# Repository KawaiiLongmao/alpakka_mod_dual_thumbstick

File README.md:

Development Board : rp2040 zero

初版：

GP20(Home)->GP13,GP18(CS0)->GP0,GP19(CS1)->GP1

led：上移12.5mm

r6电阻：左移21.5mm，上移4.75mm

home：上移22.5mm

滚轮：左移16mm

两摇杆间距：51.75mm

修订1：

GP20(Home)->GP13,GP18(CS0)->GP0,GP19(CS1)->GP1

led：上移12.5mm

r6电阻：左移21.5mm，上移4.75mm

home：上移22.5mm

滚轮：左移18.5mm

左摇杆：左移2.5mm

两摇杆间距：52mm

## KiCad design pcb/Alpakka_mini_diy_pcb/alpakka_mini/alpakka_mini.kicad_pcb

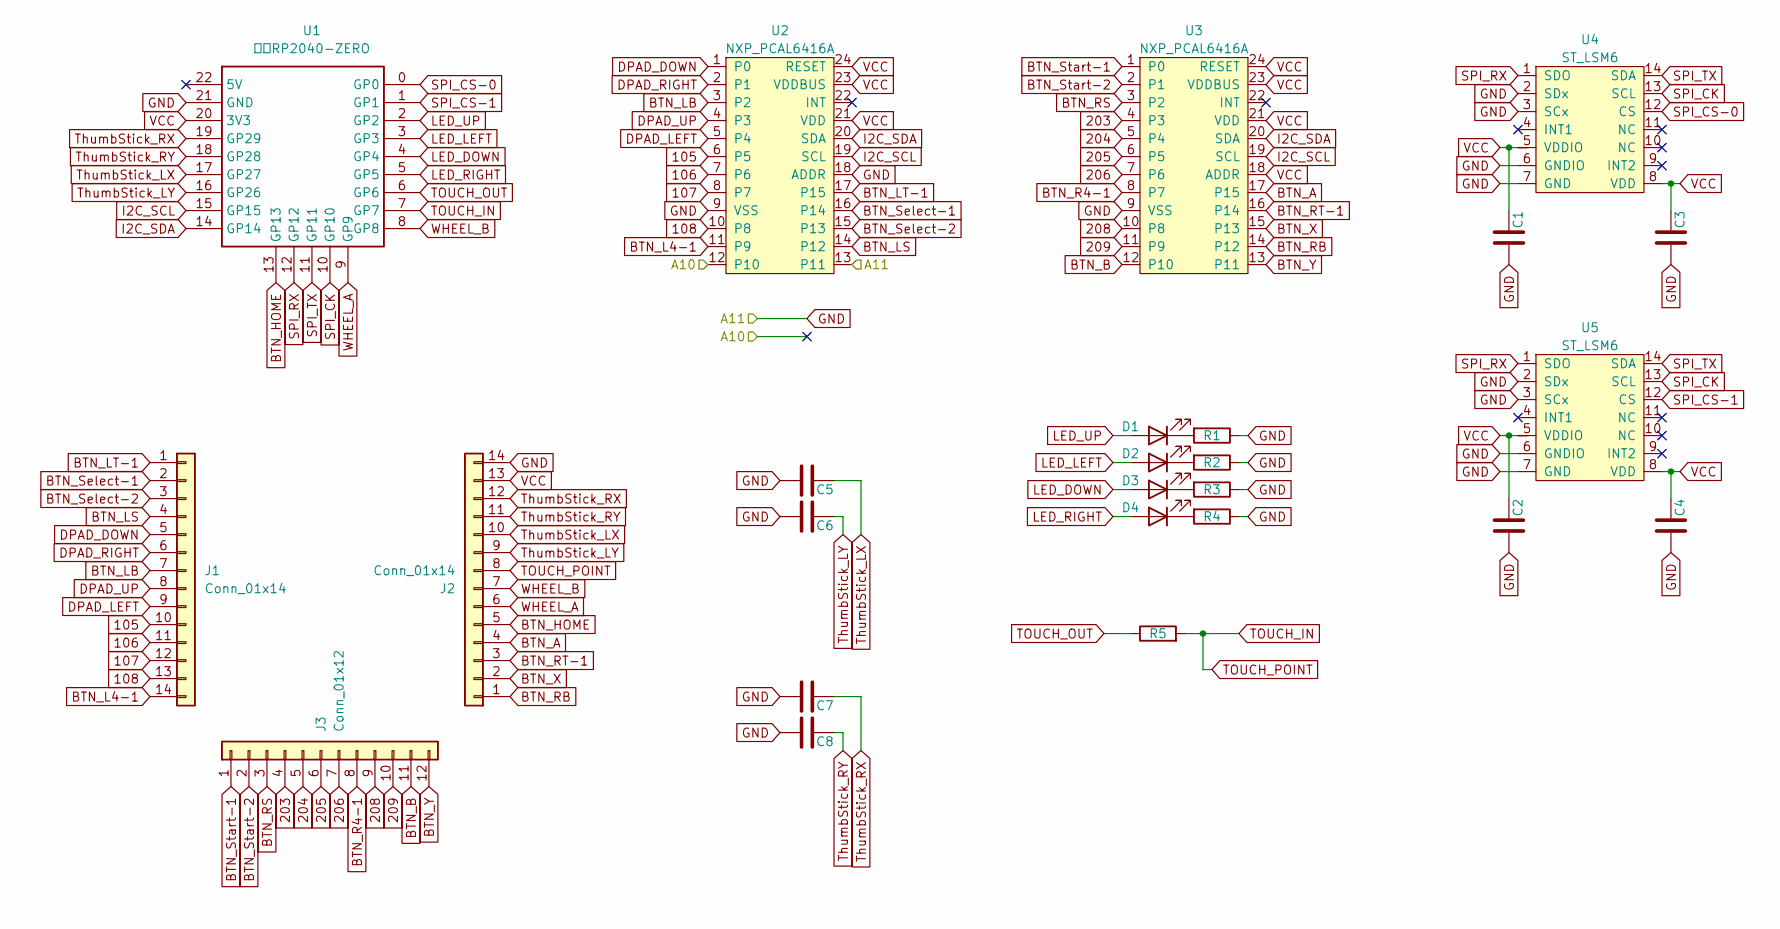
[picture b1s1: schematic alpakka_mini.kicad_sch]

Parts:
C1, C2, C3, C4, C5, C6, C7, C8: C; 0402; LCSC C1525
D1, D2, D3, D4: Diode; 0603_d; LCSC C2290
J1, J2: Conn_01x14; 邮票孔排针1x14PIN_2.54MM
J3: Conn_01x12; 邮票孔排针1x12PIN_2.54MM
R1, R2, R3, R4: R; 0603; LCSC C22950
R5: R6; 0402; LCSC C11616
U1: 微雪RP2040-ZERO; RP2040-ZERO_SMT
U2, U3: NXP_PCAL6416A; QFN24; LCSC C2652287
U4, U5: ST_LSM6; LGA14; LCSC C784817

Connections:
105: J1.10, U2.6 (P5)
106: J1.11, U2.7 (P6)
107: J1.12, U2.8 (P7)
108: J1.13, U2.10 (P8)
203: J3.4, U3.4 (P3)
204: J3.5, U3.5 (P4)
205: J3.6, U3.6 (P5)
206: J3.7, U3.7 (P6)
208: J3.9, U3.10 (P8)
209: J3.10, U3.11 (P9)
/A10: U2.12 (P10)
BTN_A: J2.4, U3.17 (P15)
BTN_B: J3.11, U3.12 (P10)
BTN_HOME: J2.5, U1.13 (GP13)
BTN_L4-1: J1.14, U2.11 (P9)
BTN_LB: J1.7, U2.3 (P2)
BTN_LS: J1.4, U2.14 (P12)
BTN_LT-1: J1.1, U2.17 (P15)
BTN_R4-1: J3.8, U3.8 (P7)
BTN_RB: J2.1, U3.14 (P12)
BTN_RS: J3.3, U3.3 (P2)
BTN_RT-1: J2.3, U3.16 (P14)
BTN_Select-1: J1.2, U2.16 (P14)
BTN_Select-2: J1.3, U2.15 (P13)
BTN_Start-1: J3.1, U3.1 (P0)
BTN_Start-2: J3.2, U3.2 (P1)
BTN_X: J2.2, U3.15 (P13)
BTN_Y: J3.12, U3.13 (P11)
DPAD_DOWN: J1.5, U2.1 (P0)
DPAD_LEFT: J1.9, U2.5 (P4)
DPAD_RIGHT: J1.6, U2.2 (P1)
DPAD_UP: J1.8, U2.4 (P3)
GND: C1.1, C2.1, C3.1, C4.1, C5.1, C6.1, C7.1, C8.1, J2.14, R1.1, R2.1, R3.1, R4.1, U1.21 (GND), U2.9 (VSS), U2.13 (P11), U2.18 (ADDR), U3.9 (VSS), U4.2 (SDx), U4.3 (SCx), U4.6 (GNDIO), U4.7 (GND), U5.2 (SDx), U5.3 (SCx), U5.6 (GNDIO), U5.7 (GND)
I2C_SCL: U1.15 (GP15), U2.19 (SCL), U3.19 (SCL)
I2C_SDA: U1.14 (GP14), U2.20 (SDA), U3.20 (SDA)
LED_DOWN: D3.2 (A), U1.4 (GP4)
LED_LEFT: D2.2 (A), U1.3 (GP3)
LED_RIGHT: D4.2 (A), U1.5 (GP5)
LED_UP: D1.2 (A), U1.2 (GP2)
unnamed: D1.1 (K), R1.2
unnamed: D2.1 (K), R2.2
unnamed: D3.1 (K), R3.2
unnamed: D4.1 (K), R4.2
SPI_CK: U1.10 (GP10), U4.13 (SCL), U5.13 (SCL)
SPI_CS-0: U1.0 (GP0), U4.12 (CS)
SPI_CS-1: U1.1 (GP1), U5.12 (CS)
SPI_RX: U1.12 (GP12), U4.1 (SDO), U5.1 (SDO)
SPI_TX: U1.11 (GP11), U4.14 (SDA), U5.14 (SDA)
TOUCH_IN: J2.8, R5.2, U1.7 (GP7)
TOUCH_OUT: R5.1, U1.6 (GP6)
ThumbStick_LX: C5.2, J2.10, U1.17 (GP27)
ThumbStick_LY: C6.2, J2.9, U1.16 (GP26)
ThumbStick_RX: C7.2, J2.12, U1.19 (GP29)
ThumbStick_RY: C8.2, J2.11, U1.18 (GP28)
VCC: C1.2, C2.2, C3.2, C4.2, J2.13, U1.20 (3V3), U2.21 (VDD), U2.23 (VDDBUS), U2.24 (RESET), U3.18 (ADDR), U3.21 (VDD), U3.23 (VDDBUS), U3.24 (RESET), U4.5 (VDDIO), U4.8 (VDD), U5.5 (VDDIO), U5.8 (VDD)
WHEEL_A: J2.6, U1.9 (GP9)
WHEEL_B: J2.7, U1.8 (GP8)

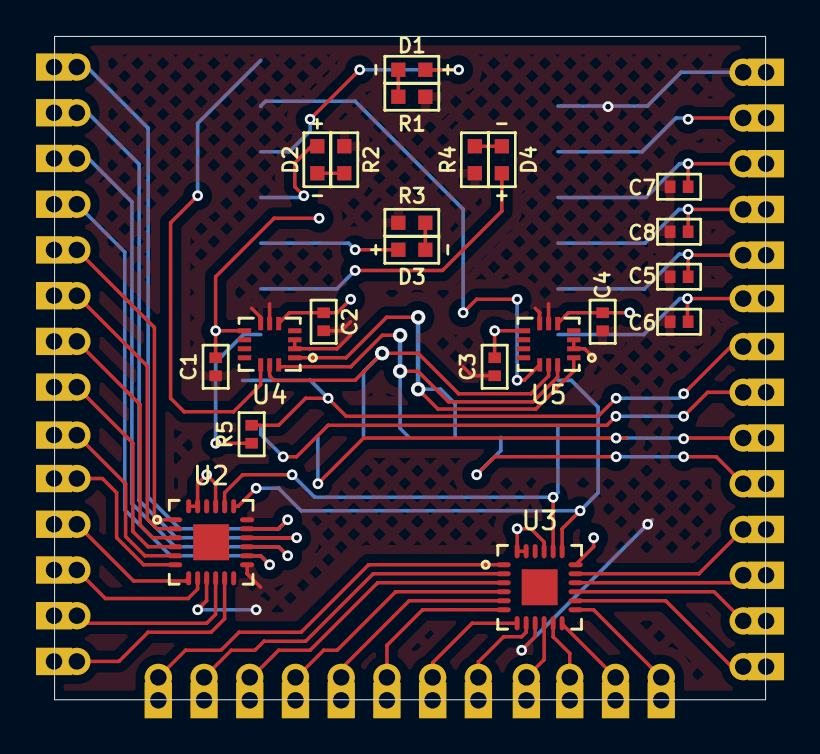
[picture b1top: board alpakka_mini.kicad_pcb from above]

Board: 2 copper layers, 39.5 x 36.9 mm, 25 parts (1 on the bottom side), 56 nets.

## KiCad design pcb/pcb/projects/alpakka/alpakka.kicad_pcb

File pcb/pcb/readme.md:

# Alpakka PCB

*Alpakka controller Printed Circuit Board reference design*

## Project links
- [Alpakka Manual](https://inputlabs.io/devices/alpakka/manual).
- [Alpakka Firmware](https://github.com/inputlabs/alpakka_firmware).
- [Alpakka PCB](https://github.com/inputlabs/alpakka_pcb). _(you are here)_
- [Alpakka 3D-print](https://github.com/inputlabs/alpakka_case).
- [Input Labs Roadmap](https://github.com/orgs/inputlabs/projects/2/views/2).

## Previews

## Order a PCB from the reference design
For ordering a reference design PCB (with no modifications) is possible to use the pre-built [order files](https://github.com/inputlabs/alpakka_pcb/releases). Check the [manual](https://inputlabs.io/devices/alpakka/manual/diy_pcb) for step-by-step instructions.

## Modify the schematics and PCB

### Dependencies
- [KiCad 8](https://www.kicad.org)

### Change components for SMT pick & place

- Open `.kicad_sch` file in Schematics editor.
- Go to menu `Tools` → `Edit symbol fields`
- Group by field `Group`
- Change id references (`LCSC id` for [JLCPCB](https://jlcpcb.com)).

### Generate order files from sources
- Copy `plugins/kicad_ilo_export.py` into KiCad plugins folder (PCB editor → menu `Tools` → `External plugins` → `Reveal plugins folder`).
- Open `.kicad_pcb` file in PCB editor.
- Use menu `Edit` → `Fill all zones`
- Go to menu `Tools` → `External plugins` → `Refresh plugins`
- Go to menu `Tools` → `External plugins` → `Input Labs: export`
- Files are generated into `order/`

### If the plugin does not load correctly
- Open `Preferences` → `Action plugins`
- Check that the plugin is installed correctly / check errors.

### Procedural zones
Consolidated zones increase `.kicad_pcb` file size significantly, so instead is recommended to load and save the project without consolidation:

- After loading the PCB project: `Edit` → `Fill all zones`.
- Before saving the PCB project: `Edit` → `Unfill all zones`.

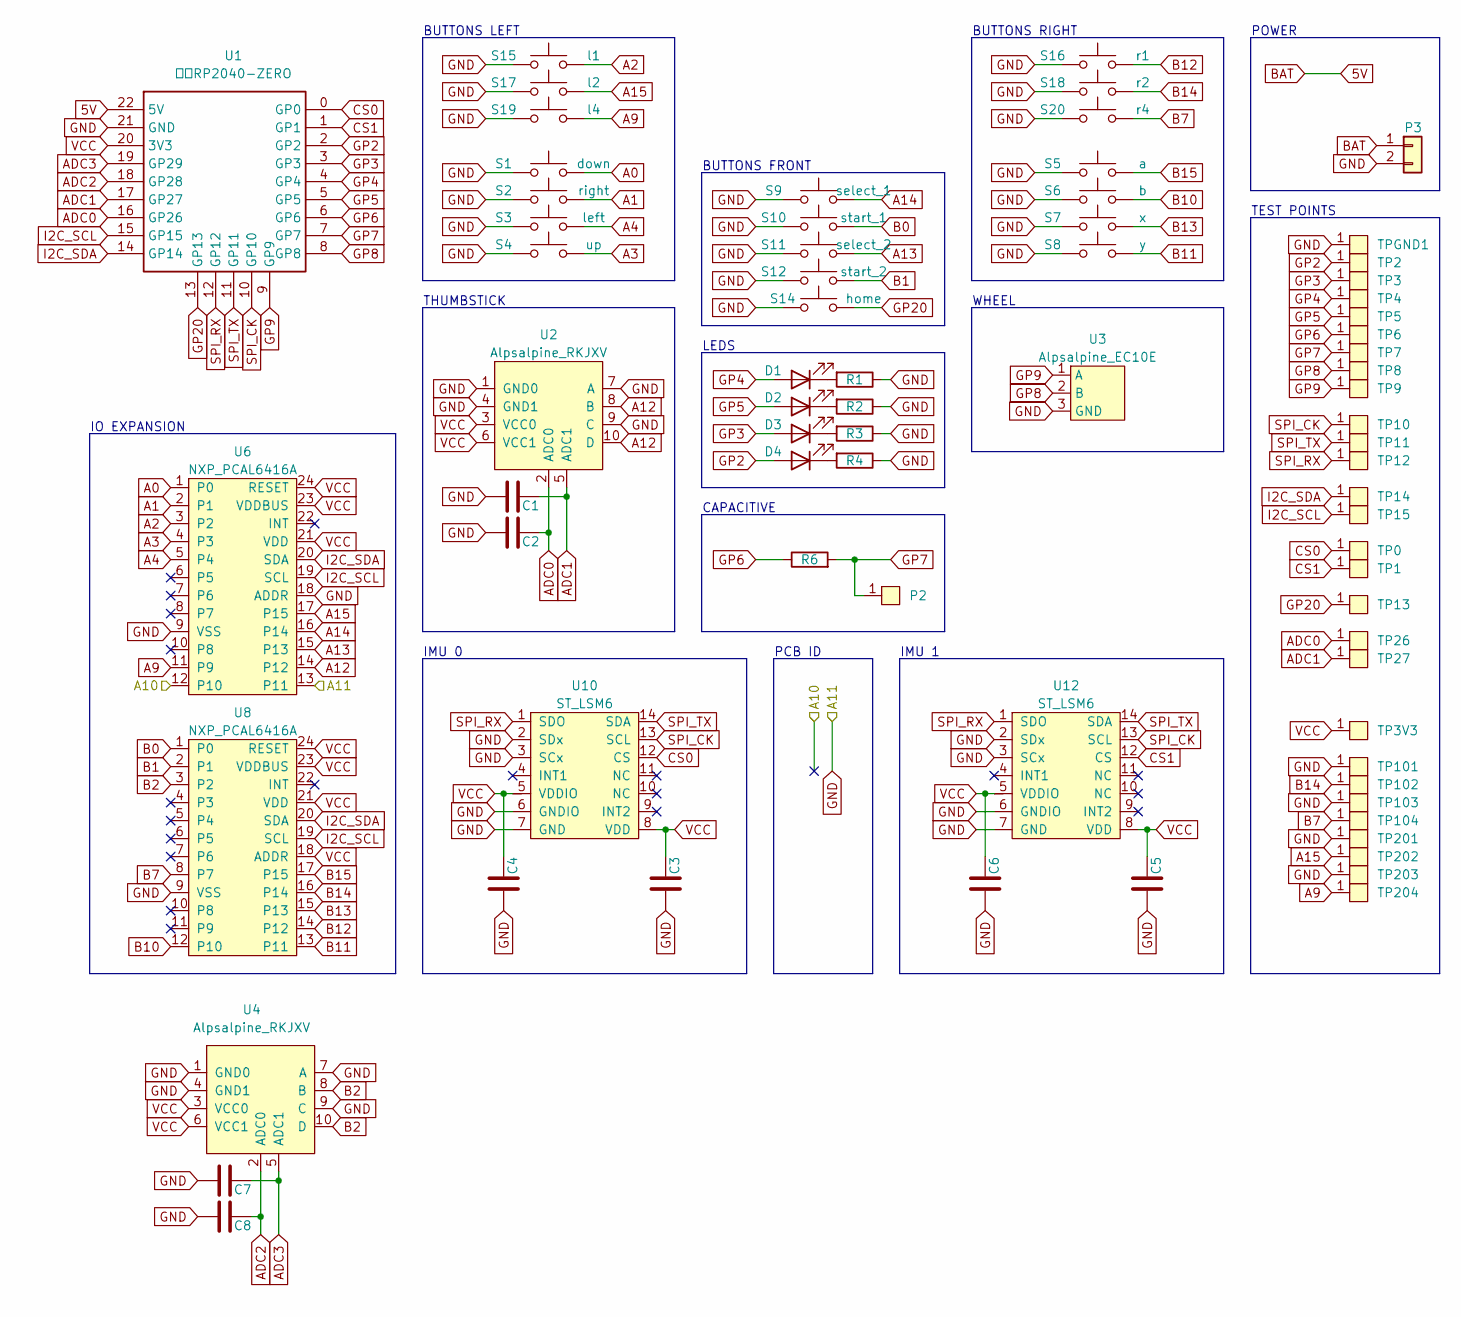
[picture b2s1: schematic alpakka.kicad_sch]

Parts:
C1, C2, C3, C4, C5, C6, C7, C8: C; 0402; LCSC C1525
D1, D2, D3, D4: Diode; 0603_d; LCSC C2290
P2: Endpoint; HRO_BC-25-3P; LCSC C707322
P3: Conn_01x02; JST_PH_2_TH
R1, R2, R3, R4: R; 0603; LCSC C22950
R6: R6; 0402; LCSC C11616
S1: down; Alpsalpine_SKPM; LCSC C115348
S2: right; Alpsalpine_SKPM; LCSC C115348
S3: left; Alpsalpine_SKPM; LCSC C115348
S4: up; Alpsalpine_SKPM; LCSC C115348
S5: a; Alpsalpine_SKPM; LCSC C115348
S6: b; Alpsalpine_SKPM; LCSC C115348
S7: x; Alpsalpine_SKPM; LCSC C115348
S8: y; Alpsalpine_SKPM; LCSC C115348
S9: select_1; Alpsalpine_SKPM; LCSC C115348
S10: start_1; Alpsalpine_SKPM; LCSC C115348
S11: select_2; Alpsalpine_SKPM; LCSC C115348
S12: start_2; Alpsalpine_SKPM; LCSC C115348
S14: home; Alpsalpine_SKPM; LCSC C115348
S15: l1; Alpsalpine_SKHHL; LCSC C125031
S16: r1; Alpsalpine_SKHHL; LCSC C125031
S17: l2; Alpsalpine_SKQG; LCSC C202424
S18: r2; Alpsalpine_SKQG; LCSC C202424
S19: l4; Alpsalpine_SKQG; LCSC C202424
S20: r4; Alpsalpine_SKQG; LCSC C202424
TP0, TP1, TP2, TP3, TP3V3, TP4, TP5, TP6, TP7, TP8, TP9, TP10, TP11, TP12, TP13, TP14, TP15, TP26, TP27, TP101, TP102, TP103, TP104, TP201, TP202, TP203, TP204: Endpoint; Pad_1mm
TPGND1: Endpoint; Pad_1mm
U1: 微雪RP2040-ZERO; PICOMINI
U2: Alpsalpine_RKJXV; Alpsalpine_RKJXV122400R; LCSC C918854
U3: Alpsalpine_EC10E; LCSC C110291
U4: Alpsalpine_RKJXV; Alpsalpine_RKJXV122400R
U6, U8: NXP_PCAL6416A; QFN24; LCSC C2652287
U10, U12: ST_LSM6; LGA14; LCSC C784817

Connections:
5V: P3.1, U1.22 (5V)
/A10: U6.12 (P10)
A0: S1.2, U6.1 (P0)
A1: S2.2, U6.2 (P1)
A2: S15.2, U6.3 (P2)
A3: S4.2, U6.4 (P3)
A4: S3.2, U6.5 (P4)
A9: S19.2, TP204.1, U6.11 (P9)
A12: U2.8 (B), U2.10 (D), U6.14 (P12)
A13: S11.2, U6.15 (P13)
A14: S9.2, U6.16 (P14)
A15: S17.2, TP202.1, U6.17 (P15)
ADC0: C2.2, TP26.1, U1.16 (GP26), U2.2 (ADC0)
ADC1: C1.2, TP27.1, U1.17 (GP27), U2.5 (ADC1)
ADC2: C8.2, U1.18 (GP28), U4.2 (ADC0)
ADC3: C7.2, U1.19 (GP29), U4.5 (ADC1)
B0: S10.2, U8.1 (P0)
B1: S12.2, U8.2 (P1)
B2: U4.8 (B), U4.10 (D), U8.3 (P2)
B7: S20.2, TP104.1, U8.8 (P7)
B10: S6.2, U8.12 (P10)
B11: S8.2, U8.13 (P11)
B12: S16.2, U8.14 (P12)
B13: S7.2, U8.15 (P13)
B14: S18.2, TP102.1, U8.16 (P14)
B15: S5.2, U8.17 (P15)
CS0: TP0.1, U1.0 (GP0), U10.12 (CS)
CS1: TP1.1, U1.1 (GP1), U12.12 (CS)
GND: C1.1, C2.1, C3.1, C4.1, C5.1, C6.1, C7.1, C8.1, P3.2, R1.1, R2.1, R3.1, R4.1, S1.1, S2.1, S3.1, S4.1, S5.1, S6.1, S7.1, S8.1, S9.1, S10.1, S11.1, S12.1, S14.1, S15.1, S16.1, S17.1, S18.1, S19.1, S20.1, TP101.1, TP103.1, TP201.1, TP203.1, TPGND1.1, U1.21 (GND), U2.1 (GND0), U2.4 (GND1), U2.7 (A), U2.9 (C), U3.3 (GND), U4.1 (GND0), U4.4 (GND1), U4.7 (A), U4.9 (C), U6.9 (VSS), U6.13 (P11), U6.18 (ADDR), U8.9 (VSS), U10.2 (SDx), U10.3 (SCx), U10.6 (GNDIO), U10.7 (GND), U12.2 (SDx), U12.3 (SCx), U12.6 (GNDIO), U12.7 (GND)
GP2: D4.2 (A), TP2.1, U1.2 (GP2)
GP3: D3.2 (A), TP3.1, U1.3 (GP3)
GP4: D1.2 (A), TP4.1, U1.4 (GP4)
GP5: D2.2 (A), TP5.1, U1.5 (GP5)
GP6: R6.1, TP6.1, U1.6 (GP6)
GP7: P2.1, R6.2, TP7.1, U1.7 (GP7)
GP8: TP8.1, U1.8 (GP8), U3.2 (B)
GP9: TP9.1, U1.9 (GP9), U3.1 (A)
GP20: S14.2, TP13.1, U1.13 (GP13)
I2C_SCL: TP15.1, U1.15 (GP15), U6.19 (SCL), U8.19 (SCL)
I2C_SDA: TP14.1, U1.14 (GP14), U6.20 (SDA), U8.20 (SDA)
unnamed: D1.1 (K), R1.2
unnamed: D2.1 (K), R2.2
unnamed: D3.1 (K), R3.2
unnamed: D4.1 (K), R4.2
SPI_CK: TP10.1, U1.10 (GP10), U10.13 (SCL), U12.13 (SCL)
SPI_RX: TP12.1, U1.12 (GP12), U10.1 (SDO), U12.1 (SDO)
SPI_TX: TP11.1, U1.11 (GP11), U10.14 (SDA), U12.14 (SDA)
VCC: C3.2, C4.2, C5.2, C6.2, TP3V3.1, U1.20 (3V3), U2.3 (VCC0), U2.6 (VCC1), U4.3 (VCC0), U4.6 (VCC1), U6.21 (VDD), U6.23 (VDDBUS), U6.24 (RESET), U8.18 (ADDR), U8.21 (VDD), U8.23 (VDDBUS), U8.24 (RESET), U10.5 (VDDIO), U10.8 (VDD), U12.5 (VDDIO), U12.8 (VDD)

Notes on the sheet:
WHEEL
THUMBSTICK
IMU 0
PCB ID
IMU 1
BUTTONS FRONT
TEST POINTS
CAPACITIVE
IO EXPANSION
LEDS
BUTTONS LEFT
BUTTONS RIGHT
POWER

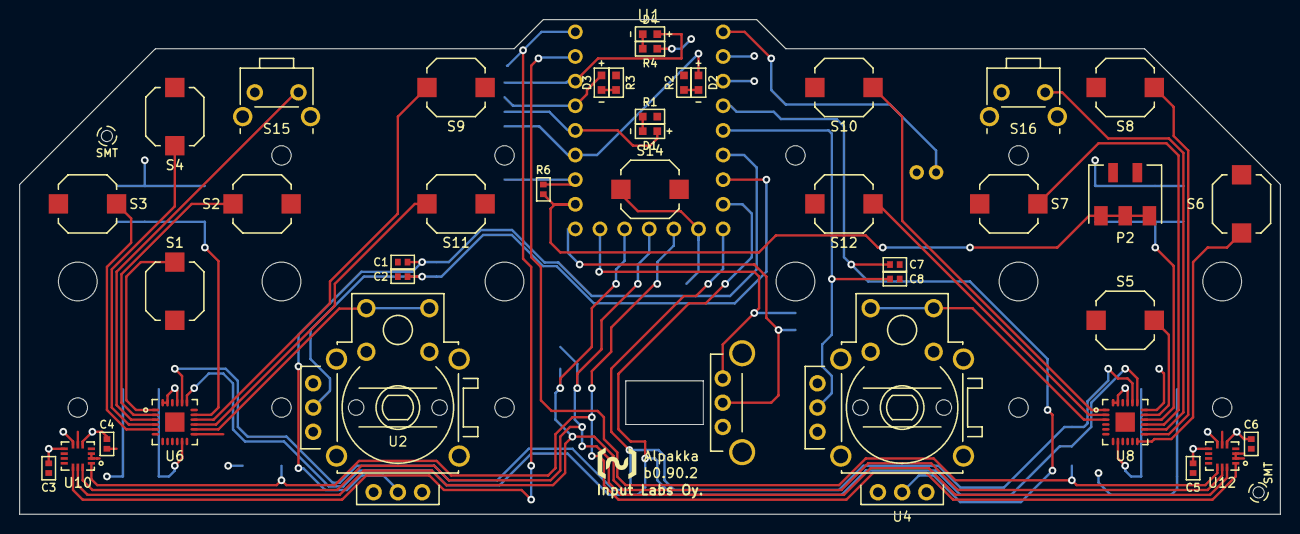
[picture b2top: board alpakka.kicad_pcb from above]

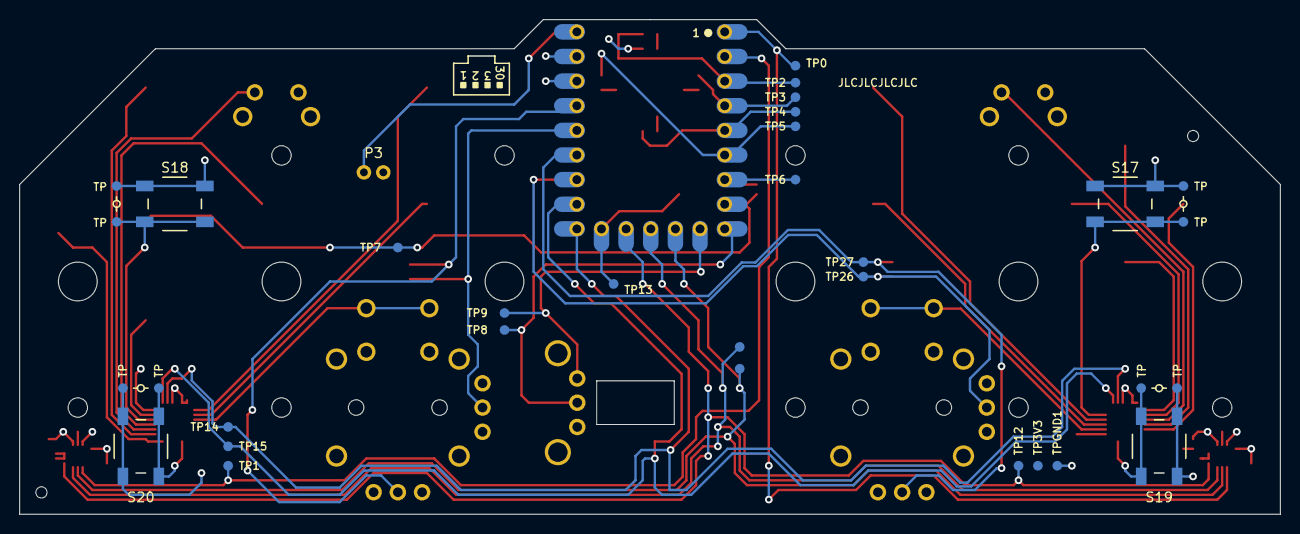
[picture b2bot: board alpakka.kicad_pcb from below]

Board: 2 copper layers, 130.0 x 51.0 mm, 74 parts (34 on the bottom side), 47 nets.

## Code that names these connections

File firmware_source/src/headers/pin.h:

// SPDX-License-Identifier: GPL-2.0-only
// Copyright (C) 2022, Input Labs Oy.

/*
Pin numbers from 0 to 29 are RP2040 GPIOs.
Pin numbers from 100 to 115 are IO Expander 1, from pin 0 to pin 15.
Pin numbers from 200 to 215 are IO Expander 2, from pin 0 to pin 15.
*/

#pragma once

// Groups.
#define PIN_GROUP_BOARD 1
#define PIN_GROUP_BOARD_END 99
#define PIN_GROUP_IO_0 100
#define PIN_GROUP_IO_0_END 199
#define PIN_GROUP_IO_1 200
#define PIN_GROUP_IO_1_END 249
#define PIN_ADC_FIRST 26

// Pico.
#ifdef DEVICE_ALPAKKA_V0
#define PIN_FUNC 0
#define PIN_LED_UP 2
#define PIN_LED_LEFT 3
#define PIN_LED_DOWN 4
#define PIN_LED_RIGHT 5
#define PIN_TOUCH_OUT 6
#define PIN_TOUCH_IN 7
#define PIN_ROTARY_B 8
#define PIN_ROTARY_A 9
#define PIN_SPI_CK 10
#define PIN_SPI_TX 11
#define PIN_SPI_RX 12
#define PIN_I2C_SDA 14
#define PIN_I2C_SCL 15
#define PIN_LED_BOARD 25
#define PIN_THUMBSTICK_LY 26
#define PIN_THUMBSTICK_LX 27
#if DEVICE_ALPAKKA_V0 == 1
#define PIN_HOME 20
#define PIN_SPI_CS0 18
#define PIN_SPI_CS1 19
#define PIN_THUMBSTICK_RY 0
#define PIN_THUMBSTICK_RX 0
#else
#define PIN_HOME 13
#define PIN_SPI_CS0 0
#define PIN_SPI_CS1 1
#define PIN_THUMBSTICK_RY 28
#define PIN_THUMBSTICK_RX 29
#endif
// Expanders.
#define PIN_SELECT_1 114
#define PIN_SELECT_2 113
#define PIN_DPAD_LEFT 104
#define PIN_DPAD_RIGHT 101
#define PIN_DPAD_UP 103
#define PIN_DPAD_DOWN 100
#define PIN_L1 102
#define PIN_L2 115
#define PIN_L3 112
#define PIN_L4 109
#define PIN_PCBGEN_0 111
#define PIN_PCBGEN_1 110
#define PIN_START_1 200
#define PIN_START_2 201
#define PIN_A 215
#define PIN_B 210
#define PIN_X 213
#define PIN_Y 211
#define PIN_R1 212
#define PIN_R2 214
#define PIN_R4 207
#if DEVICE_ALPAKKA_V0 == 1
#define PIN_DHAT_LEFT 203
#define PIN_DHAT_RIGHT 205
#define PIN_DHAT_UP 206
#define PIN_DHAT_DOWN 202
#define PIN_R3 204
#else
#define PIN_DHAT_LEFT 0
#define PIN_DHAT_RIGHT 0
#define PIN_DHAT_UP 0
#define PIN_DHAT_DOWN 0
#define PIN_R3 202
#endif
#endif

// Marmota.
#ifdef DEVICE_HAS_MARMOTA
#define PIN_FUNC 2
#define PIN_LED_BOARD 3
#define PIN_SPI_CS1 4      //  5 (rc1)
#define PIN_SPI_CS0 5      //  6 (rc1)
#define PIN_LED_LEFT 6     //  7 (rc1)
#define PIN_LED_DOWN 7     //  8 (rc1)
#define PIN_LED_RIGHT 8    //  9 (rc1)
#define PIN_LED_UP 9       // 10 (rc1)
#define PIN_ROTARY_B 10    // 11 (rc1)
#define PIN_ROTARY_A 11    // 12 (rc1)
#define PIN_TOUCH_IN 12    // 13 (rc1)
#define PIN_TOUCH_OUT 13   //  4 (rc1)
#define PIN_BATT_STAT_1 14 // 15 (rc1)
#define PIN_DC_POWER_SAVE 15
#define PIN_SPI_RX 16
#define PIN_ESP_BOOT 17
#define PIN_SPI_CK 18
#define PIN_SPI_TX 19
#define PIN_UART1_TX 20
#define PIN_UART1_RX 21
#define PIN_I2C_SDA 22
#define PIN_I2C_SCL 23
#define PIN_HOME 24
#define PIN_ESP_ENABLE 25
#if MOD_LINGHU
#define PIN_THUMBSTICK_RY 27
#define PIN_THUMBSTICK_RX 26
#else
#define PIN_THUMBSTICK_RY 26
#define PIN_THUMBSTICK_RX 27
#endif
#define PIN_THUMBSTICK_LX 29
#define PIN_THUMBSTICK_LY 28
// Expanders.
#define PIN_SELECT_1 114
#define PIN_SELECT_2 110
#define PIN_DPAD_LEFT 104
#define PIN_DPAD_RIGHT 101
#define PIN_DPAD_UP 103
#define PIN_DPAD_DOWN 100
#define PIN_L1 102
#define PIN_L2 115
#define PIN_L3 109
#define PIN_L4 108
#define PIN_PCBGEN_0 111
#define PIN_PCBGEN_1 113
#define PIN_START_1 200
#define PIN_START_2 201
#define PIN_A 215
#define PIN_B 210
#define PIN_X 213
#define PIN_Y 211
#define PIN_DHAT_LEFT 203
#define PIN_DHAT_RIGHT 205
#define PIN_DHAT_UP 206
#define PIN_DHAT_DOWN 204
#define PIN_R1 212
#define PIN_R2 214
#define PIN_R3 202
#define PIN_R4 207
#endif

// SPECIAL PINS.
#define PIN_GROUP_SPECIAL 250
#define PIN_NONE 255
#define PIN_VIRTUAL 254 // Buttons without any hardware associated to them.

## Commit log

2024-10-02 1.1.2
2024-10-03 readme
2024-10-07 1.1.3
2025-09-16 20250916
2025-09-30 20250930
2025-10-13 20251013
2025-10-13 20251014
2025-10-31 20251031
2026-02-04 20260204
2026-02-04 20260205
2026-03-10 20260311
